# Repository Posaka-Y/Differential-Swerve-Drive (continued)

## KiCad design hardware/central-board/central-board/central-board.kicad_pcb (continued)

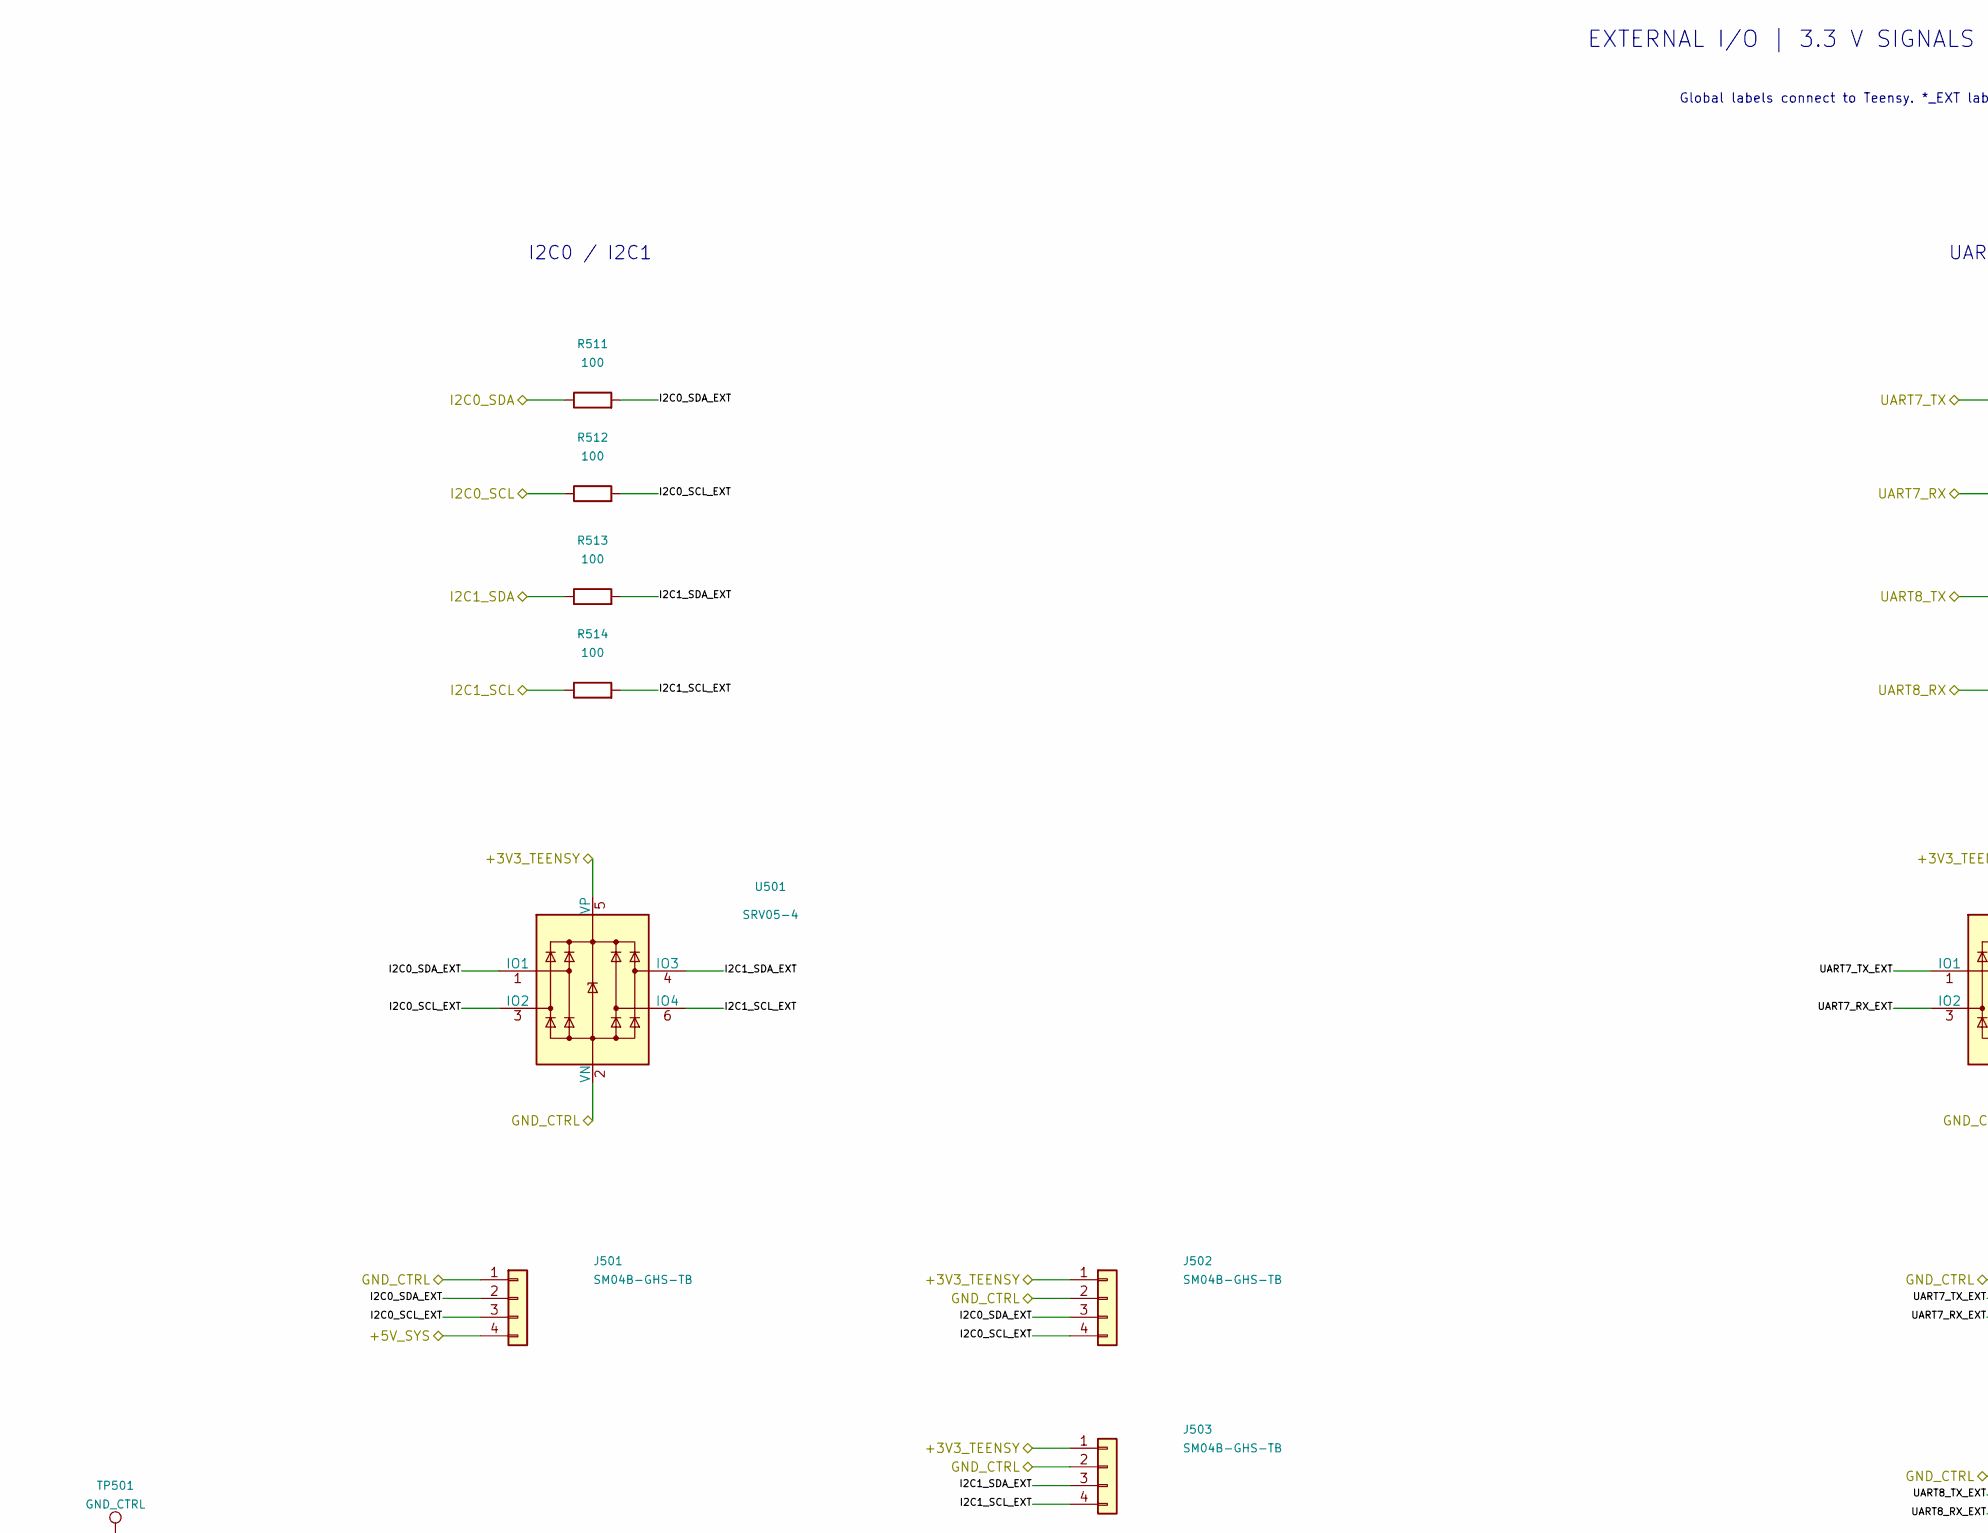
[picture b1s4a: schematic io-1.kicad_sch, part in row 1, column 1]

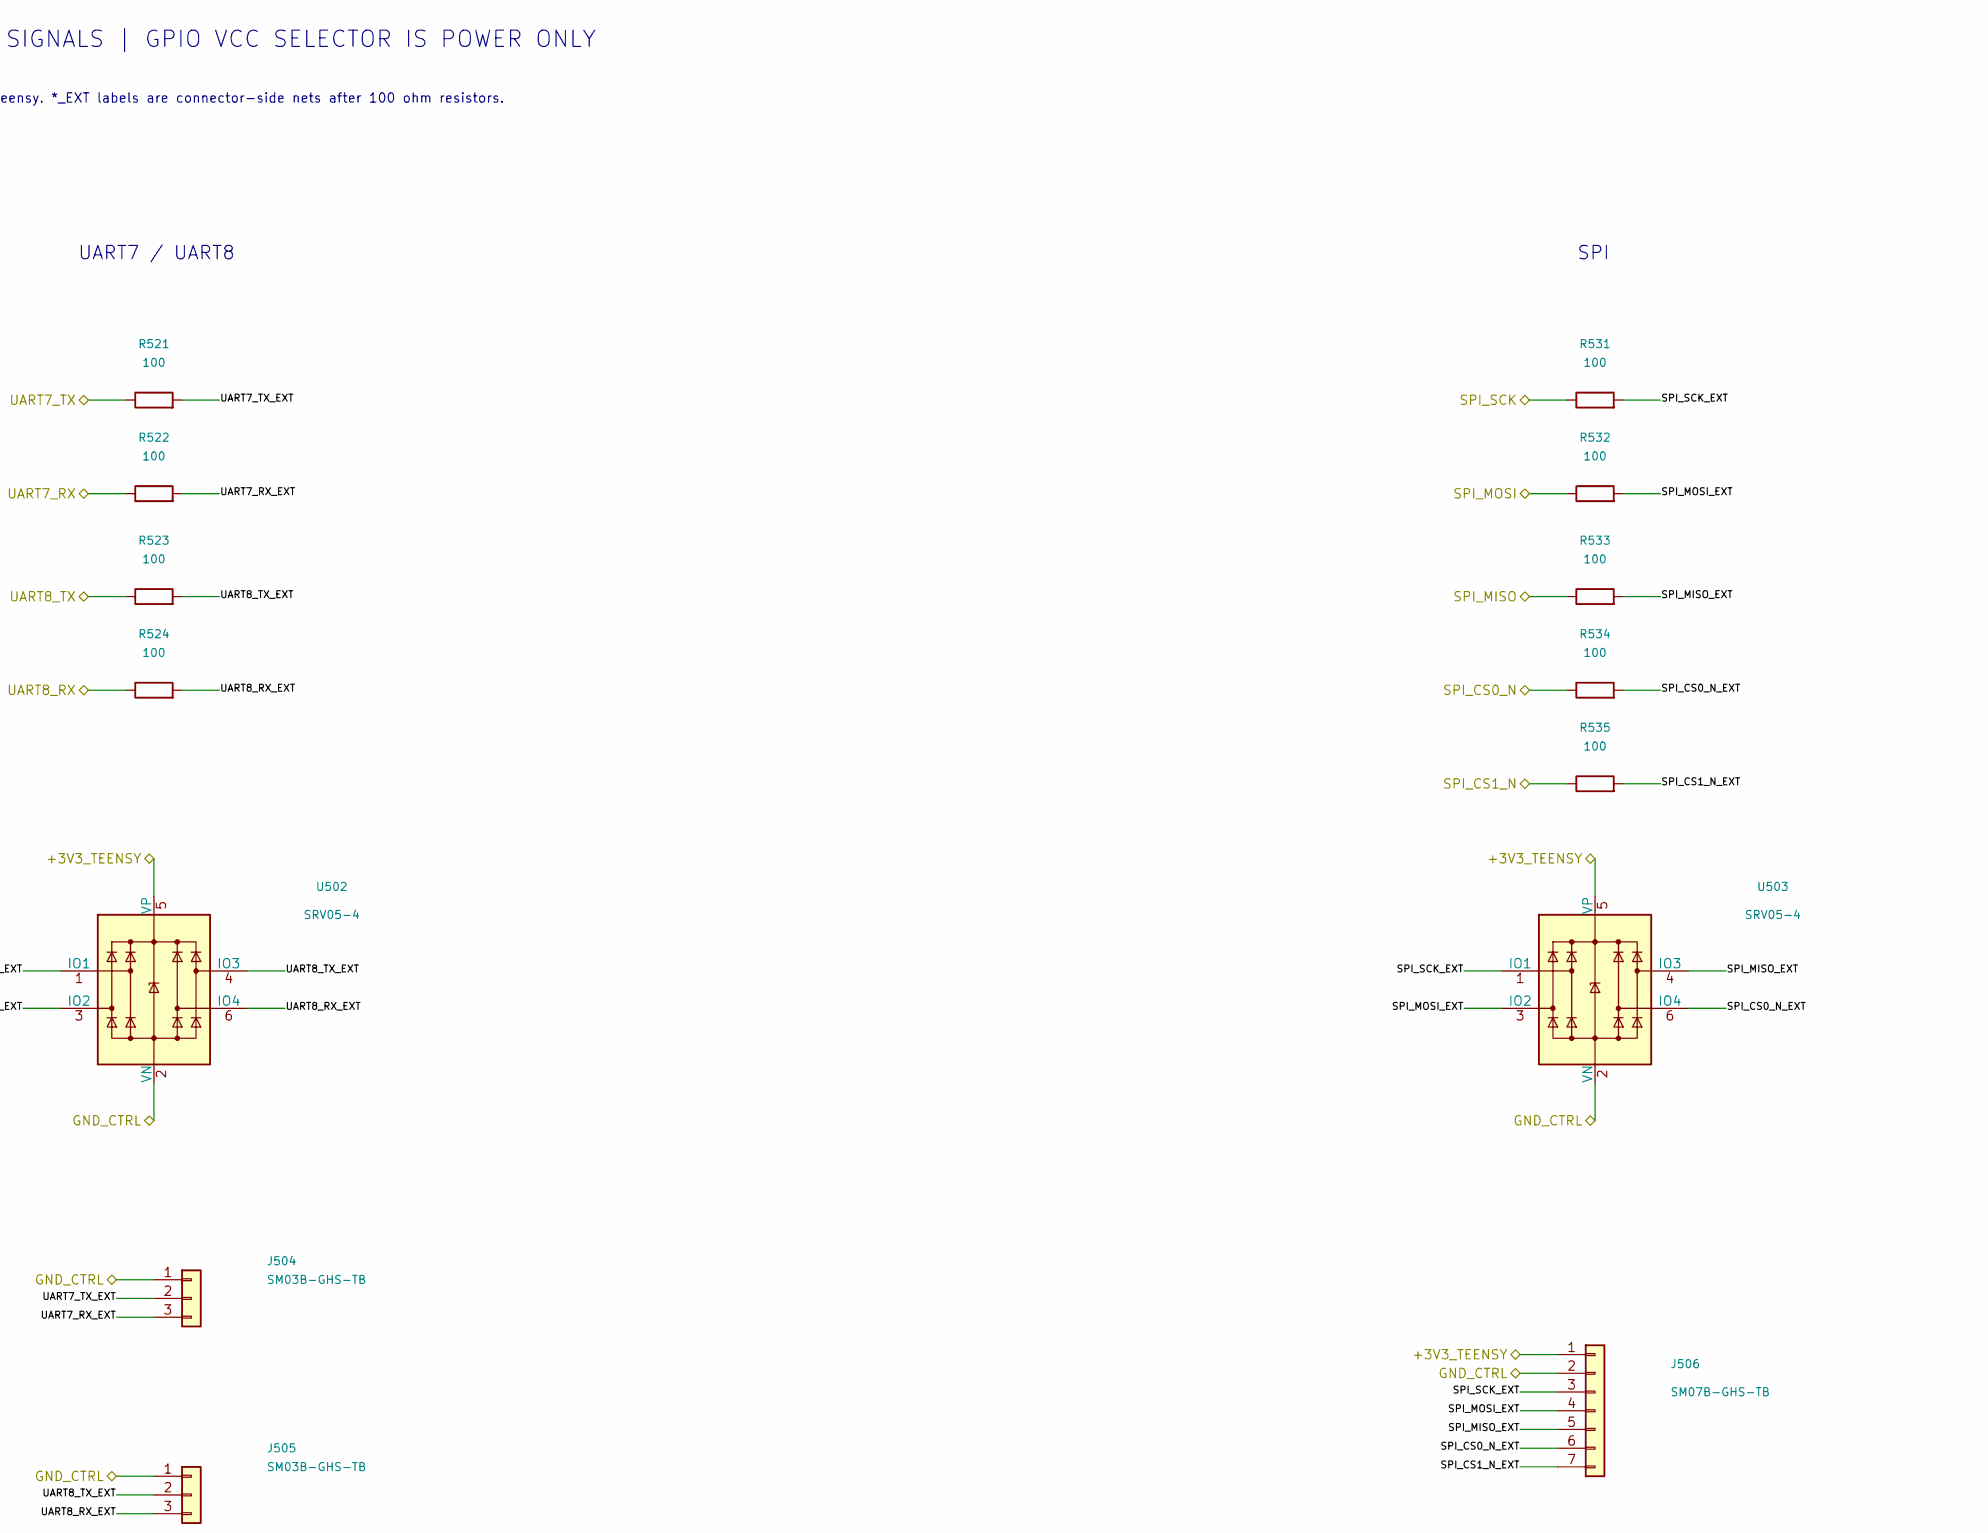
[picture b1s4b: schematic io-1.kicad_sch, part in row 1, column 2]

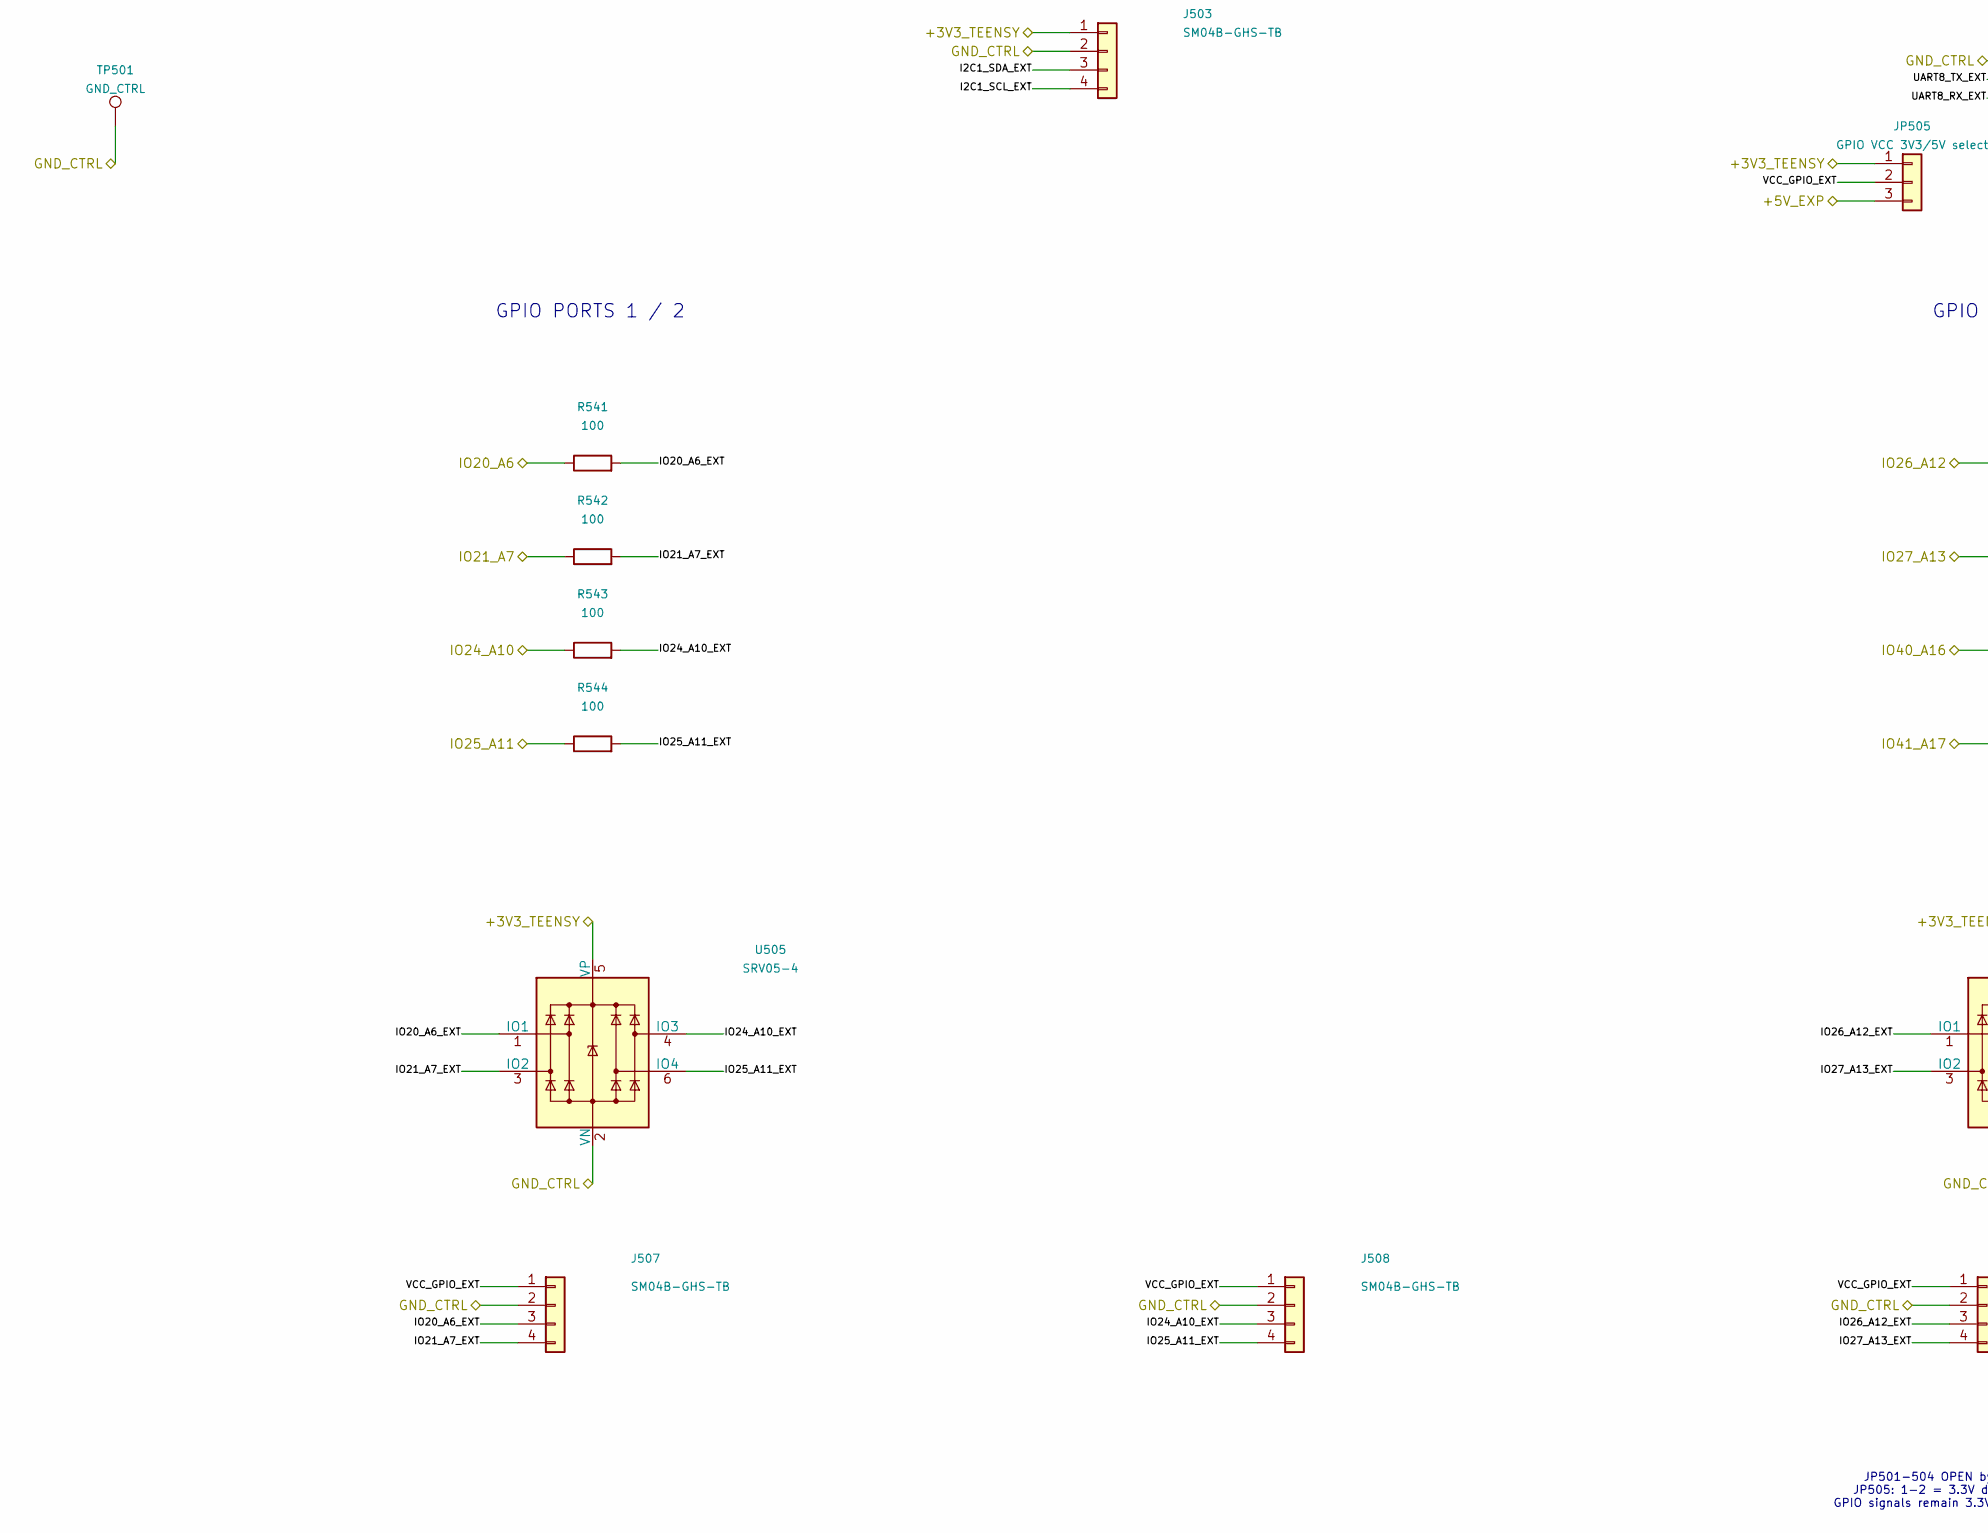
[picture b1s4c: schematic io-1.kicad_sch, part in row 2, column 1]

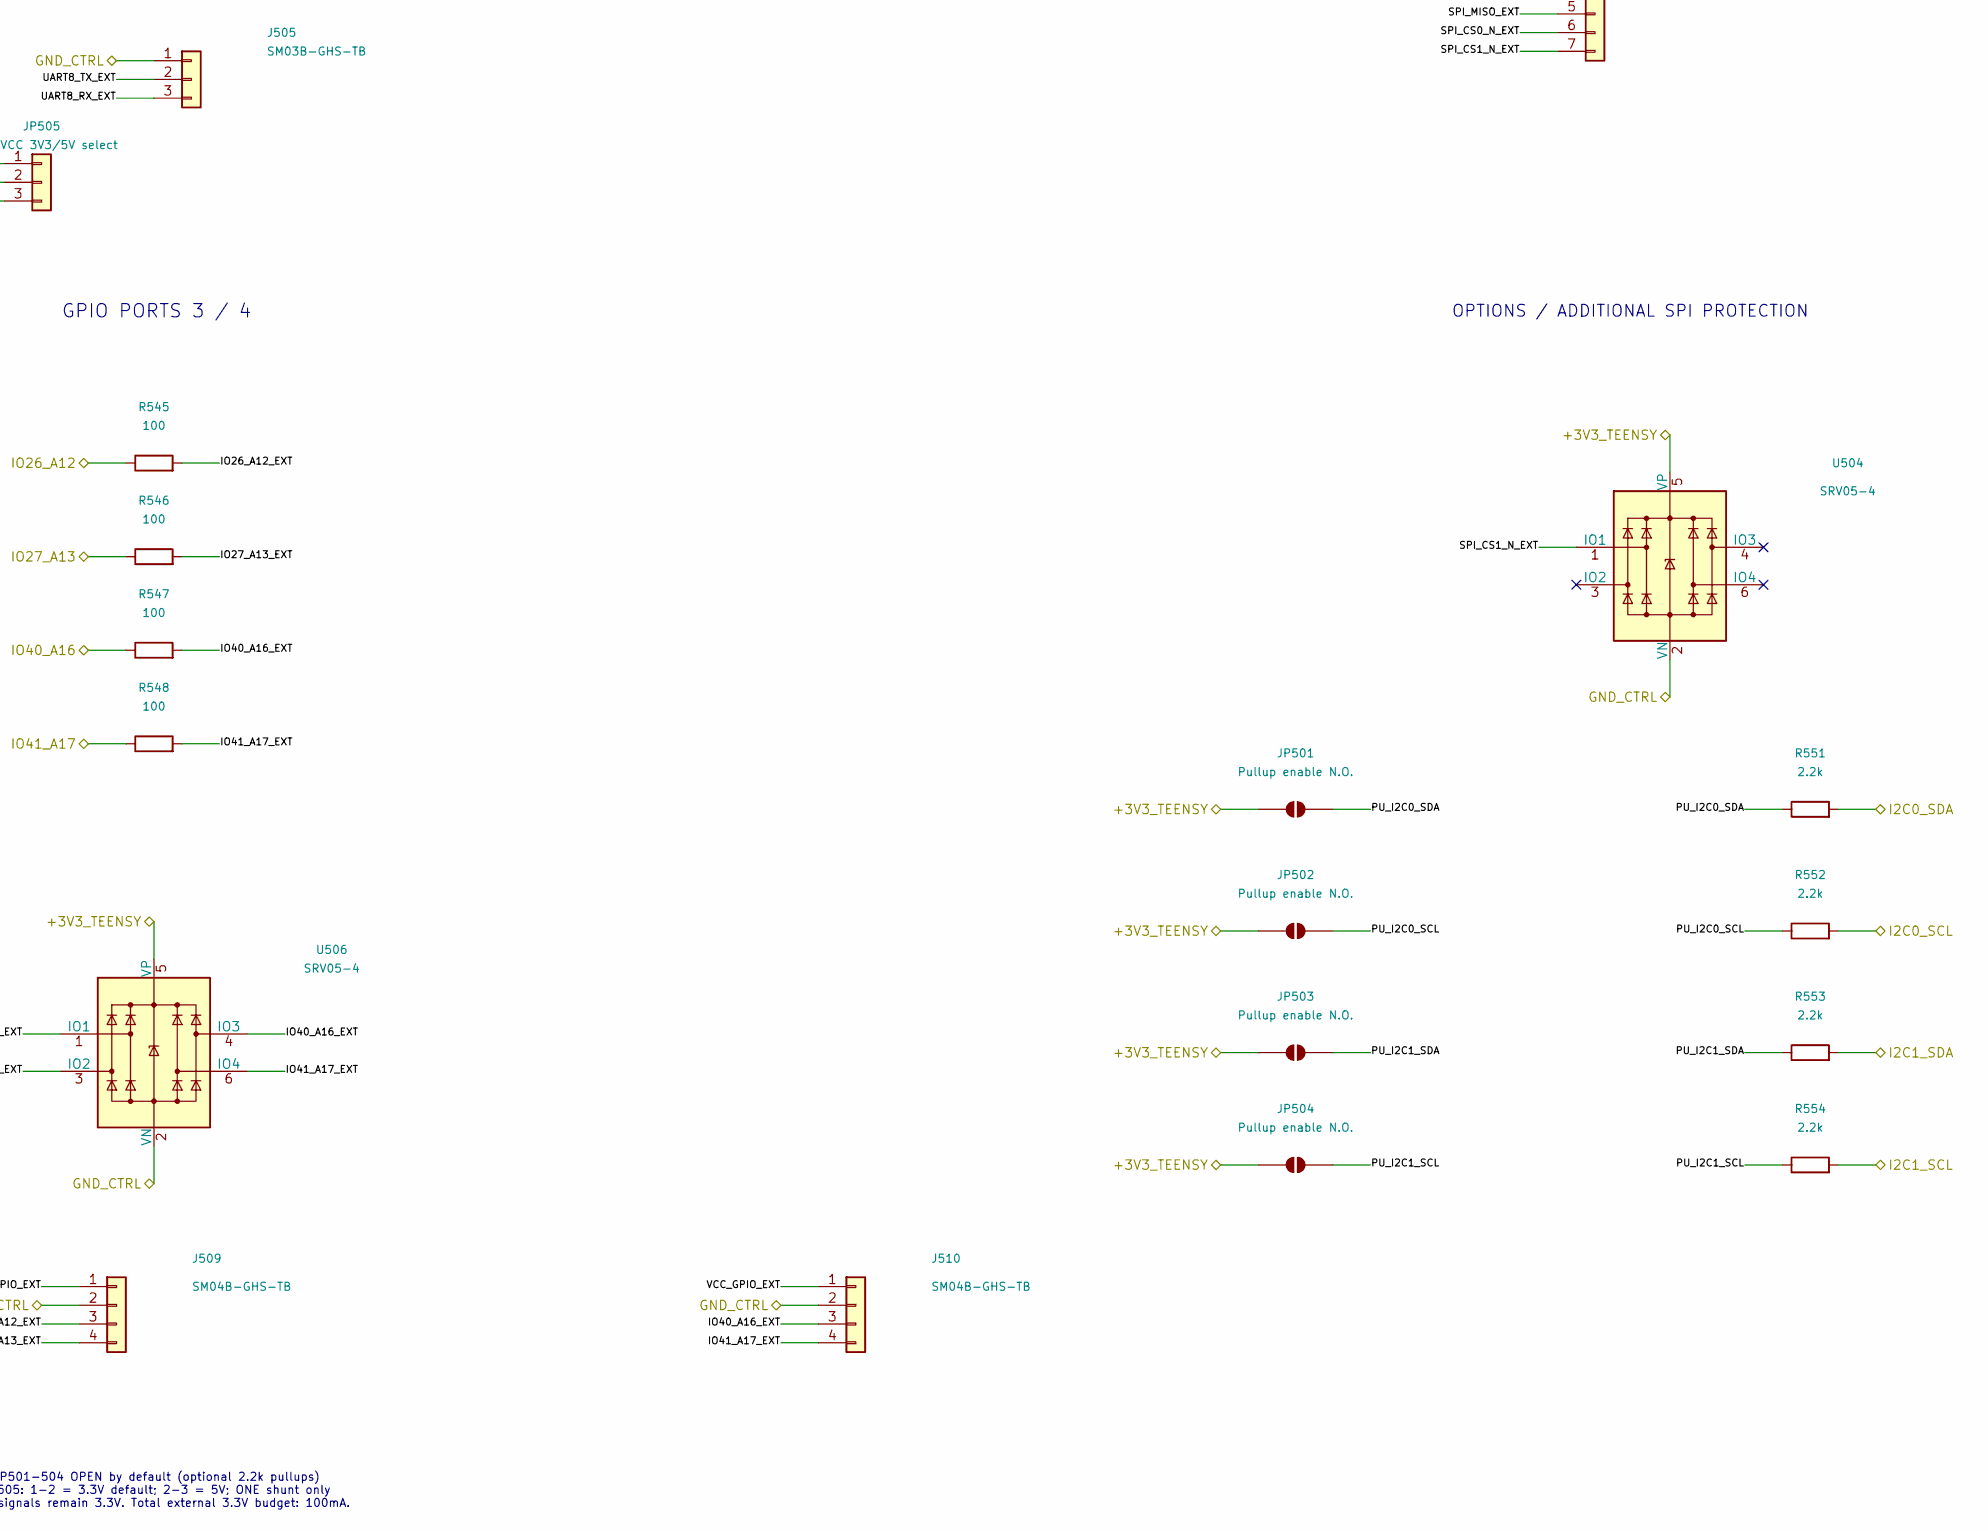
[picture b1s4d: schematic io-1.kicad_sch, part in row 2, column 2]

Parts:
J501, J502, J503, J507, J508, J509, J510: SM04B-GHS-TB; JST_GH_SM04B-GHS-TB_1x04-1MP_P1.25mm_Horizontal
J504, J505: SM03B-GHS-TB; JST_GH_SM03B-GHS-TB_1x03-1MP_P1.25mm_Horizontal
J506: SM07B-GHS-TB; JST_GH_SM07B-GHS-TB_1x07-1MP_P1.25mm_Horizontal
JP501, JP502, JP503, JP504: Pullup enable N.O.; SolderJumper-2_P1.3mm_Open_RoundedPad1.0x1.5mm
JP505: GPIO VCC 3V3/5V select; PinHeader_1x03_P2.54mm_Vertical
R511, R512, R513, R514, R521, R522, R523, R524, R531, R532, R533, R534, R535, R541, R542, R543, R544, R545, R546, R547, R548: 100; R_0603_1608Metric
R551, R552, R553, R554: 2.2k; R_0603_1608Metric
TP501: GND_CTRL; Harwin_S1751-46R
U501, U502, U503, U504, U505, U506: SRV05-4; SOT-23-6

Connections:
/+3V3_TEENSY: J502.1, J503.1, J506.1, JP501.1 (A), JP502.1 (A), JP503.1 (A), JP504.1 (A), JP505.1, U501.5 (VP), U502.5 (VP), U503.5 (VP), U504.5 (VP), U505.5 (VP), U506.5 (VP); also elsewhere on the board
/+5V_EXP: JP505.3; also elsewhere on the board
/+5V_SYS: J501.4; also elsewhere on the board
/I2C0_SCL: R512.1, R552.2; also elsewhere on the board
/I2C0_SDA: R511.1, R551.2; also elsewhere on the board
/I2C1_SCL: R514.1, R554.2; also elsewhere on the board
/I2C1_SDA: R513.1, R553.2; also elsewhere on the board
/IO20_A6: R541.1; also elsewhere on the board
/IO21_A7: R542.1; also elsewhere on the board
/IO24_A10: R543.1; also elsewhere on the board
/IO25_A11: R544.1; also elsewhere on the board
/IO26_A12: R545.1; also elsewhere on the board
/IO27_A13: R546.1; also elsewhere on the board
/IO40_A16: R547.1; also elsewhere on the board
/IO41_A17: R548.1; also elsewhere on the board
/Matek battery monitor / expansion I/O (1)/I2C0_SCL_EXT: J501.3, J502.4, R512.2, U501.3 (IO2)
/Matek battery monitor / expansion I/O (1)/I2C0_SDA_EXT: J501.2, J502.3, R511.2, U501.1 (IO1)
/Matek battery monitor / expansion I/O (1)/I2C1_SCL_EXT: J503.4, R514.2, U501.6 (IO4)
/Matek battery monitor / expansion I/O (1)/I2C1_SDA_EXT: J503.3, R513.2, U501.4 (IO3)
/Matek battery monitor / expansion I/O (1)/IO20_A6_EXT: J507.3, R541.2, U505.1 (IO1)
/Matek battery monitor / expansion I/O (1)/IO21_A7_EXT: J507.4, R542.2, U505.3 (IO2)
/Matek battery monitor / expansion I/O (1)/IO24_A10_EXT: J508.3, R543.2, U505.4 (IO3)
/Matek battery monitor / expansion I/O (1)/IO25_A11_EXT: J508.4, R544.2, U505.6 (IO4)
/Matek battery monitor / expansion I/O (1)/IO26_A12_EXT: J509.3, R545.2, U506.1 (IO1)
/Matek battery monitor / expansion I/O (1)/IO27_A13_EXT: J509.4, R546.2, U506.3 (IO2)
/Matek battery monitor / expansion I/O (1)/IO40_A16_EXT: J510.3, R547.2, U506.4 (IO3)
/Matek battery monitor / expansion I/O (1)/IO41_A17_EXT: J510.4, R548.2, U506.6 (IO4)
/Matek battery monitor / expansion I/O (1)/PU_I2C0_SCL: JP502.2 (B), R552.1
/Matek battery monitor / expansion I/O (1)/PU_I2C0_SDA: JP501.2 (B), R551.1
/Matek battery monitor / expansion I/O (1)/PU_I2C1_SCL: JP504.2 (B), R554.1
/Matek battery monitor / expansion I/O (1)/PU_I2C1_SDA: JP503.2 (B), R553.1
/Matek battery monitor / expansion I/O (1)/SPI_CS0_N_EXT: J506.6, R534.2, U503.6 (IO4)
/Matek battery monitor / expansion I/O (1)/SPI_CS1_N_EXT: J506.7, R535.2, U504.1 (IO1)
/Matek battery monitor / expansion I/O (1)/SPI_MISO_EXT: J506.5, R533.2, U503.4 (IO3)
/Matek battery monitor / expansion I/O (1)/SPI_MOSI_EXT: J506.4, R532.2, U503.3 (IO2)
/Matek battery monitor / expansion I/O (1)/SPI_SCK_EXT: J506.3, R531.2, U503.1 (IO1)
/Matek battery monitor / expansion I/O (1)/UART7_RX_EXT: J504.3, R522.2, U502.3 (IO2)
/Matek battery monitor / expansion I/O (1)/UART7_TX_EXT: J504.2, R521.2, U502.1 (IO1)
/Matek battery monitor / expansion I/O (1)/UART8_RX_EXT: J505.3, R524.2, U502.6 (IO4)
/Matek battery monitor / expansion I/O (1)/UART8_TX_EXT: J505.2, R523.2, U502.4 (IO3)
/Matek battery monitor / expansion I/O (1)/VCC_GPIO_EXT: J507.1, J508.1, J509.1, J510.1, JP505.2
/SPI_CS0_N: R534.1; also elsewhere on the board
/SPI_CS1_N: R535.1; also elsewhere on the board
/SPI_MISO: R533.1; also elsewhere on the board
/SPI_MOSI: R532.1; also elsewhere on the board
/SPI_SCK: R531.1; also elsewhere on the board
/UART7_RX: R522.1; also elsewhere on the board
/UART7_TX: R521.1; also elsewhere on the board
/UART8_RX: R524.1; also elsewhere on the board
/UART8_TX: R523.1; also elsewhere on the board
GND_CTRL: J501.1, J502.2, J503.2, J504.1, J505.1, J506.2, J507.2, J508.2, J509.2, J510.2, TP501.1 (1_1), U501.2 (VN), U502.2 (VN), U503.2 (VN), U504.2 (VN), U505.2 (VN), U506.2 (VN); also elsewhere on the board

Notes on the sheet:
OPTIONS / ADDITIONAL SPI PROTECTION
UART7 / UART8
I2C0 / I2C1
JP501-504 OPEN by default (optional 2.2k pullups) JP505: 1-2 = 3.3V default; 2-3 = 5V; ONE shunt only GPIO signals remain 3.3V. Total external 3.3V budget: 100mA.
GPIO PORTS 3 / 4
SPI
GPIO PORTS 1 / 2
Global labels connect to Teensy. *_EXT labels are connector-side nets after 100 ohm resistors.
EXTERNAL I/O | 3.3 V SIGNALS | GPIO VCC SELECTOR IS POWER ONLY

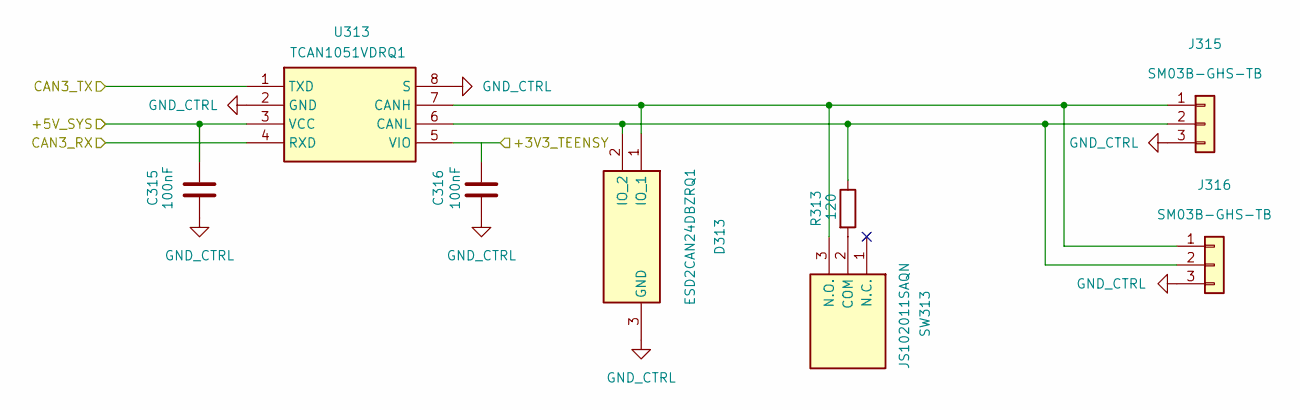
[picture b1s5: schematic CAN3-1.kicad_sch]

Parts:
C315, C316: 100nF; C_0603_1608Metric
D313: ESD2CAN24DBZRQ1; SOT-23
J315, J316: SM03B-GHS-TB; JST_GH_SM03B-GHS-TB_1x03-1MP_P1.25mm_Horizontal
R313: 120; R_0603_1608Metric
SW313: JS102011SAQN
U313: TCAN1051VDRQ1; SOIC-8_3.9x4.9mm_P1.27mm

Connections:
/+3V3_TEENSY: C316.1, U313.5 (VIO); also elsewhere on the board
/+5V_SYS: C315.1, U313.3 (VCC); also elsewhere on the board
/CAN3_RX: U313.4 (RXD); also elsewhere on the board
/CAN3_TX: U313.1 (TXD); also elsewhere on the board
GND_CTRL: C315.2, C316.2, D313.3 (GND), J315.3, J316.3, U313.2 (GND), U313.8 (S); also elsewhere on the board
unnamed: D313.1 (IO_1), J315.1, J316.1, SW313.3 (N.O.), U313.7 (CANH)
unnamed: D313.2 (IO_2), J315.2, J316.2, R313.1, U313.6 (CANL)
unnamed: R313.2, SW313.2 (COM)

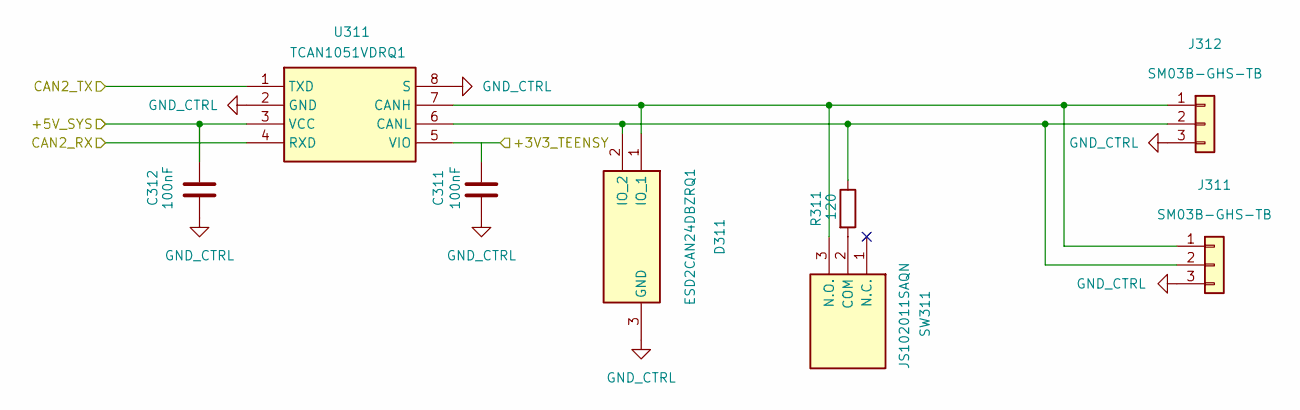
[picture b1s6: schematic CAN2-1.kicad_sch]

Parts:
C311, C312: 100nF; C_0603_1608Metric
D311: ESD2CAN24DBZRQ1; SOT-23
J311, J312: SM03B-GHS-TB; JST_GH_SM03B-GHS-TB_1x03-1MP_P1.25mm_Horizontal
R311: 120; R_0603_1608Metric
SW311: JS102011SAQN
U311: TCAN1051VDRQ1; SOIC-8_3.9x4.9mm_P1.27mm

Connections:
/+3V3_TEENSY: C311.1, U311.5 (VIO); also elsewhere on the board
/+5V_SYS: C312.1, U311.3 (VCC); also elsewhere on the board
/CAN2_RX: U311.4 (RXD); also elsewhere on the board
/CAN2_TX: U311.1 (TXD); also elsewhere on the board
GND_CTRL: C311.2, C312.2, D311.3 (GND), J311.3, J312.3, U311.2 (GND), U311.8 (S); also elsewhere on the board
unnamed: D311.1 (IO_1), J311.1, J312.1, SW311.3 (N.O.), U311.7 (CANH)
unnamed: D311.2 (IO_2), J311.2, J312.2, R311.1, U311.6 (CANL)
unnamed: R311.2, SW311.2 (COM)

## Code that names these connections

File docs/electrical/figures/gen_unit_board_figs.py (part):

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    d.add(elm.Ground())
    note(d, (0.4, -3.0), 'ハーネス側 GND_CTRL = 基板内 GND')

    # pin1 -> PWR_5V_IN
    d.add(elm.Line().at(j101.p1).right().length(2.2).label('PWR_5V_IN', loc='top'))
    din = d.add(elm.Dot())
    d.add(elm.Capacitor().at(din.center).down().length(1.8).label('C101\n2.2uF以上', loc='bottom', fontsize=9))
    d.add(elm.Ground())
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    d.add(elm.Wire('-|').at(u101.CEN).to(dv.center))
    note(d, (7.2, -1.3), 'CE_N=VOUT 接続は意図的\n(RPP+RCB、TI DS 8.3節)\n標準アプリ図(CE_N=GND)と異なる')

    d.add(elm.Line().at(dv.center).right().length(1.2).label('PWR_5V', loc='top'))
    dc1 = d.add(elm.Dot())
    d.add(elm.Capacitor().at(dc1.center).down().length(1.8).label('C201\n100nF', loc='bottom', fontsize=9))
    d.add(elm.Ground())
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        size=(3.0, 5.4)).at((0, 0)).anchor('TXD').label('U401\nTCAN1051VDRQ1\n(SOIC-8)', loc='top', fontsize=9))

    # MCU side
    d.add(elm.Line(arrow='->').at((-3.5, 0)).to(u401.TXD).label('COMM_TX', loc='top', fontsize=9))
    netlabel(d, (-3.5, 0), 'U301 PA12\n(FDCAN1_TX)', loc='left')
    ry = u401.RXD.y
    d.add(elm.Line(arrow='->').at(u401.RXD).to((-3.5, ry)).label('COMM_RX', loc='top', fontsize=9))
    netlabel(d, (-3.5, ry), 'U301 PA11\n(FDCAN1_RX)', loc='left')

    # VCC (5V) + C401
    vy = u401.VCC.y
    d.add(elm.Line().at(u401.VCC).to((-2.6, vy)))
    dvcc = d.add(elm.Dot().at((-1.6, vy)))
    netlabel(d, (-2.6, vy), 'PWR_5V', loc='left')
    d.add(elm.Capacitor().at(dvcc.center).down().length(1.4).label('C401\n100nF', loc='bottom', fontsize=8))
    d.add(elm.Ground())
    # VIO (3V3) + C402
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    ly = u401.CANL.y     # y of COMM_B
    hx0 = u401.CANH.x
    lx0 = u401.CANL.x
    d.add(elm.Line().at(u401.CANH).right().length(2.0).label('COMM_A', loc='top', fontsize=10))
    d.add(elm.Line().right().length(10.0))
    hx_end = hx0 + 12.0
    d.add(elm.Line().at(u401.CANL).right().length(2.0).label('COMM_B', loc='top', fontsize=10))
    d.add(elm.Line().right().length(9.0))
    lx_end = lx0 + 11.0

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    note(d, (hx_end + 0.2, hy - 8.4), 'J401/J402はIN/OUT区別なく並列直結(パススルー)。\nGND(3番)は省略しない')

    note(d, (-4.9, ly - 7.6),
         'C620側 (U501/D501/R501/SW501): 同一回路。C620_CAN_TX=PB13(FDCAN2_TX)、C620_CAN_RX=PB12(FDCAN2_RX)、\n'
         '外部ネット名 C620_CAN_H/L。コネクタ型番・個数・ピン順は未確定(正本6章#1)のため描いていない。')
    save(d, 'unit-board-block2')

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
    # --- NRST ---
    y2 = -5.2
    netlabel(d, (0, y2), 'U301 PG10-NRST (pin 7)', loc='left')
    d.add(elm.Line().at((0, y2)).right().length(1.6))
    dn = d.add(elm.Dot())
    d.add(elm.Capacitor().at(dn.center).down().length(1.6).label('C313\n100nF', loc='bottom', fontsize=8))
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
    # --- BOOT0 ---
    x3 = 9.0
    netlabel(d, (x3, y2), 'U301 PB8-BOOT0', loc='left')
    d.add(elm.Line().at((x3, y2)).right().length(1.6))
    db = d.add(elm.Dot())
    d.add(elm.Resistor().at(db.center).down().length(2.0).label('R303\n10kΩ', loc='bottom', fontsize=8))
    d.add(elm.Ground())
    d.add(elm.Line().at(db.center).right().length(1.8))
    netlabel(d, d.here, 'TP(BOOT0)+隣接TP(3V3)', loc='right')
    note(d, (x3 + 0.2, y2 - 3.0), 'pull-down。PB8はGPIOに使わない')

    save(d, 'unit-board-block4')

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    d = schemdraw.Drawing(show=False)
    d.config(fontsize=10, font=FONT)
    d.add(elm.Label().at((0, 3.6)).label(
        'Block 5: 5V監視ADC (PA0)', loc='right', halign='left', fontsize=12))

    netlabel(d, (0, 0), 'PWR_5V', loc='left')
    d.add(elm.Resistor().at((0, 0)).right().length(2.4).label('R304 33kΩ', loc='top', fontsize=9))
    dm = d.add(elm.Dot())
    d.add(elm.Resistor().at(dm.center).down().length(2.2).label('R305\n22kΩ', loc='bottom', fontsize=9))
    d.add(elm.Ground())
    d.add(elm.Line().at(dm.center).right().length(1.6).label('ADC_5V_MON', loc='top', fontsize=10))
    dc = d.add(elm.Dot())
    d.add(elm.Capacitor().at(dc.center).down().length(2.2).label('C314\n10nF', loc='bottom', fontsize=9))
    d.add(elm.Ground())
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    d.add(elm.Line().at(dc.center).right().length(1.8))
    dd = d.add(elm.Dot())
    d.add(elm.Line().at(dd.center).right().length(1.8))
    netlabel(d, d.here, 'U301 PA0 (ADC)\nmax 2.2V (0.4倍)', loc='right')

    # BAT54S: pin1=GND, pin2=3V3, pin3=PA0
    x = dd.center.x
    d1 = d.add(elm.Schottky().at((x, 0)).up().length(1.8).label('', loc='top'))
    d.add(elm.Line().up().length(0.4))
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    d.add(elm.Label().at((x + 0.25, 0.1)).label('3', loc='right', fontsize=8))
    d.add(elm.Label().at((x + 0.25, -1.9)).label('1', loc='right', fontsize=8))
    note(d, (x + 1.6, -1.0),
         'D301 BAT54SLT1G (直列2素子)\npin1=GND / pin2=3V3 / pin3=PA0\n上下クランプ。内部ダイオード向きを\nデータシート図と必ず照合')
    note(d, (0, -4.4), '5V系がADCへ入る唯一の点。サンプリング時間は\nソースインピーダンス13.2kΩに合わせる(ファーム)')
    save(d, 'unit-board-block5')

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        .label('J601\nSM06B-GHS-TB\n(AMT22中継/横挿し)', loc='top', fontsize=9))

    d.add(elm.Line().at(j601.p1).right().length(4.6))
    netlabel(d, d.here, 'PWR_5V', loc='right')
    d.add(elm.Resistor().at(j601.p2).right().length(2.6).label('R601', loc='top', fontsize=8))
    d.add(elm.Line().right().length(2.0))
    netlabel(d, d.here, 'SPI3_SCK (U301 PC10)', loc='right')
    d.add(elm.Resistor().at(j601.p3).right().length(2.6).label('R602', loc='top', fontsize=8))
    d.add(elm.Line().right().length(2.0))
    netlabel(d, d.here, 'SPI3_MOSI (U301 PC12)', loc='right')
    d.add(elm.Line().at(j601.p4).right().length(0.4))
    d.add(elm.Ground())
    d.add(elm.Resistor().at(j601.p5).right().length(2.6).label('R603', loc='top', fontsize=8))
    d.add(elm.Line().right().length(2.0))
    netlabel(d, d.here, 'SPI3_MISO (U301 PC11)', loc='right')
    d.add(elm.Resistor().at(j601.p6).right().length(2.6).label('R604', loc='top', fontsize=8))
    d.add(elm.Line().right().length(2.0))
    netlabel(d, d.here, 'AMT22_CS_N (U301 PD2, ソフトCS)', loc='right')
    note(d, (0, -6.6),
         'AMT22と同ピン順=ストレート結線。R601-604は0603フットプリントのみ確定、\n'
         '値は未確定(初期0Ω実装が候補、正本6章#3)。5V電源・3.3V論理で直結成立')
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        elm.IcPin(name='SWCLK', pin='2', side='right', slot='5/6', anchorname='p2'),
        elm.IcPin(name='SWDIO', pin='3', side='right', slot='4/6', anchorname='p3'),
        elm.IcPin(name='NRST', pin='4', side='right', slot='3/6', anchorname='p4'),
        elm.IcPin(name='DBG_TX', pin='5', side='right', slot='2/6', anchorname='p5'),
        elm.IcPin(name='DBG_RX', pin='6', side='right', slot='1/6', anchorname='p6')],
        size=(2.4, 5.6)).at((xj, 0)).anchor('p1')
        .label('J701\nBM06B-GHS-TBT\n(デバッグ/上挿し)', loc='top', fontsize=9))
    d.add(elm.Line().at(j701.p1).right().length(0.8))
    d.add(elm.Ground())
    for pin, name in [('p2', 'SWCLK (U301 PA14)'), ('p3', 'SWDIO (U301 PA13)'),
                      ('p4', 'NRST (U301 PG10 pin7)'),
                      ('p5', 'DBG_TX (U301 PA2, LPUART1_TX)'),
                      ('p6', 'DBG_RX (U301 PA3, LPUART1_RX)')]:
        d.add(elm.Line().at(getattr(j701, pin)).right().length(1.6))
        netlabel(d, d.here, name, loc='right')
    note(d, (xj, -6.6),
         'DBG_TX/RX方向は「基板視点TX/RX」の推測=未確定(正本6章#7)。\n'
         'WeActデバッガ側と照合のこと。J701に電源ピン無し=デバッガ給電を\n'
         '基板へ入れない(意図的)。PA13/PA14はSWD専用')

    # ---- SW701 ID DIP ----
    ys = -10.0
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        .label('SW701 3bit DIP\n(型番未確定 6章#2)', loc='top', fontsize=9))
    d.add(elm.Line().at(sw.com).left().length(0.8))
    d.add(elm.Ground())
    for pin, name in [('b0', 'UNIT_ID0 (U301 PC6)'), ('b1', 'UNIT_ID1 (U301 PC7)'),
                      ('b2', 'UNIT_ID2 (U301 PC8)')]:
        d.add(elm.Line().at(getattr(sw, pin)).right().length(1.6))
        netlabel(d, d.here, name, loc='right')
    note(d, (0, ys - 3.2), '内部プルアップ、ON=GND短絡\n→ ON=Low、ファームで読み値反転')
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    # ---- LEDs ----
    xl = 10.5
    rows = [('3V3 (常時点灯)', 'R701\n1kΩ', 'D701 PWR 緑'),
            ('LED_RUN (U301 PA5)', 'R702\n1kΩ', 'D702 RUN 緑'),
            ('LED_COMM (U301 PB10)', 'R703\n1kΩ', 'D703 COMM 黄'),
            ('LED_ERR (U301 PB11)', 'R704\n1kΩ', 'D704 ERR 赤')]
    for i, (src, rr, dd) in enumerate(rows):
        y = ys + 1.2 - i * 1.9
        netlabel(d, (xl, y), src, loc='left')
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
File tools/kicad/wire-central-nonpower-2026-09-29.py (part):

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s.text('24 V LOOP & EXTERNAL CONNECTORS',135,35,1.8)
for r,x,y,l,v,nets in [
 ('J403',105,60,None,None,['+24V_CTRL_IN','GND_24V_RETURN']),
 ('J401',255,65,'Connector_Generic:Conn_01x04','TBD E-stop 4pin',['ESTOP_LOOP_OUT','ESTOP_LOOP_RETURN','ESTOP_LED_24V','GND_CTRL_LED']),
 ('J402',410,60,None,None,['ESTOP_LOOP_RETURN','COIL_NEG'])]:
    s.place(r,x,y,libid=l,value=v,footprint='' if r=='J401' else None,template='J403')
    for i,n in enumerate(nets,1):s.connect(r,i,n)
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s.text('5 V BUFFER -> 100 V MOSFET / DEFAULT OFF',420,172,1.8)
s.place('U402',350,210);s.connect('U402',1,'GND_CTRL');s.connect('U402',2,'MOTOR_PWR_EN',True)
s.connect('U402',3,'GND_CTRL');s.connect('U402',5,'+5V_SYS',True)
s.place('R414',405,210,90);a,_=s.point('U402',4);b,_=s.point('R414',1);s.wire(a,b);s.label('COIL_BUFFER_OUT',(380,210),False)
expected['U402.4']=expected['R414.1']='COIL_BUFFER_OUT'
s.place('Q401',475,210);a,_=s.point('R414',2);b,_=s.point('Q401',1);s.wire(a,b);s.label('COIL_GATE',(430,210),False)
expected['R414.2']=expected['Q401.1']='COIL_GATE'
s.connect('Q401',3,'COIL_NEG');s.connect('Q401',2,'GND_24V_RETURN')
for r,x,n in [('R413',315,'MOTOR_PWR_EN'),('R415',425,'COIL_GATE')]:
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s.place('C401',520,265);s.connect('C401',1,'+5V_SYS',True);s.connect('C401',2,'GND_CTRL')

# Explicit unfitted design blocks: no invented selected part / manufacturing footprint.
custom={'lib_id':'CentralPlacement:CoilClamp_TBD','value':'CLAMP TBD','custom_pins':[{'number':1,'name':'COIL_POS'},{'number':2,'name':'COIL_NEG'}]}
libs.add_custom(custom)
s.place('X401',465,115,libid=custom['lib_id'],value='CLAMP TBD',footprint='',template='J403')
s.connect('X401',1,'ESTOP_LOOP_RETURN');s.connect('X401',2,'COIL_NEG')
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 ('I2C0 / I2C1',100,45,[(511,'I2C0_SDA'),(512,'I2C0_SCL'),(513,'I2C1_SDA'),(514,'I2C1_SCL')],501),
 ('UART7 / UART8',295,45,[(521,'UART7_TX'),(522,'UART7_RX'),(523,'UART8_TX'),(524,'UART8_RX')],502),
 ('SPI',490,45,[(531,'SPI_SCK'),(532,'SPI_MOSI'),(533,'SPI_MISO'),(534,'SPI_CS0_N'),(535,'SPI_CS1_N')],503),
 ('GPIO PORTS 1 / 2',100,245,[(541,'IO20_A6'),(542,'IO21_A7'),(543,'IO24_A10'),(544,'IO25_A11')],505),
 ('GPIO PORTS 3 / 4',295,245,[(545,'IO26_A12'),(546,'IO27_A13'),(547,'IO40_A16'),(548,'IO41_A17')],506)]
for title,x,y,signals,tvs in groups:
    s.text(title,x,y,1.8)
    for i,(num,net) in enumerate(signals):
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
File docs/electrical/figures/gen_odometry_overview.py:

# -*- coding: utf-8 -*-
"""
Odometry board zone/block overview diagram (schemdraw SVG rendering).
Source of truth: docs/electrical/ODOMETRY_BOARD_SCHEMATIC_REFERENCE.md
  Section "1枚上の配置" / "RefDes割当" / "ブロック接続".
Generated: 2026-07-25

Box + arrow + net-name level only (no IC pin layout, no R/C values).
"""
import os
import matplotlib
from matplotlib import font_manager

FONT = 'sans-serif'
for fam in ['Yu Gothic', 'Meiryo', 'MS Gothic']:
    try:
        font_manager.findfont(fam, fallback_to_default=False)
        matplotlib.rcParams['font.family'] = [fam, 'sans-serif']
        FONT = fam
        print('using font', fam)
        break
    except Exception:
        continue

import schemdraw
import schemdraw.elements as elm
from schemdraw.elements import Rect

FIGDIR = os.path.dirname(os.path.abspath(__file__))

BOX_KW = dict(lw=1.3)


def box(d, xy, w, h, title, body='', title_size=11, body_size=9):
    x, y = xy
    d.add(Rect(corner1=(x, y), corner2=(x + w, y + h), **BOX_KW))
    d.add(elm.Label().at((x + w / 2, y + h - 0.35)).label(
        title, halign='center', valign='top', fontsize=title_size))
    if body:
        d.add(elm.Label().at((x + w / 2, y + h - 0.9)).label(
            body, halign='center', valign='top', fontsize=body_size, color='#333333'))
    return (x, y, w, h)


def arrow(d, p1, p2, label='', loc='top', fontsize=9, color='black'):
    d.add(elm.Arrow().at(p1).to(p2).color(color).label(label, loc=loc, fontsize=fontsize))


def main():
    d = schemdraw.Drawing(show=False)
    d.config(fontsize=10, font=FONT)

    d.add(elm.Label().at((0, 15.6)).label(
        'オドメトリ基板(STM32F405RGT6) ゾーン/ブロック概観図 — '
        'ODOMETRY_BOARD_SCHEMATIC_REFERENCE.md 準拠(簡易版・ピン配置/定数は省略)',
        loc='right', halign='left', fontsize=12))

    # ---------------- Top row: power chain -> CAN (100/200/300/400台) ----------------
    top_y = 12.6
    b_pwr = box(d, (0, top_y), 3.4, 2.2, 'J101 5V入力\n逆接/逆流保護', '100番台\nLM66100')
    b_ldo = box(d, (4.6, top_y), 3.4, 2.2, '3.3V LDO', '200番台\nTLV1117LV33')
    b_can = box(d, (16.4, top_y), 3.6, 2.2, 'センサーCAN', '400番台\nTCAN1051V')

    # ---------------- Mid row: Debug | MCU | IMU (700/300/600台) ----------------
    mid_y = 8.4
    b_dbg = box(d, (0, mid_y), 3.4, 2.6, 'Debug/BOOT/\nID/LED', '700番台\nSWD, UNIT_ID, LED x3')
    b_mcu = box(d, (7.4, mid_y - 0.3), 5.6, 3.2, 'STM32F405RGT6', '300番台\nF405最小回路(HSE/NRST/\nVDDA/VCAP)')
    b_imu = box(d, (16.4, mid_y), 3.6, 2.6, 'ICM-42688-P', '600番台\nSPI3 IMU')

    # ---------------- Bottom row: AMT102 x3 (500台) ----------------
    bot_y = 4.2
    b_w1 = box(d, (0, bot_y), 3.6, 2.4, 'AMT102\nWheel 1', 'J501/D501/U501\nR511-512')
    b_w2 = box(d, (5.4, bot_y), 3.6, 2.4, 'AMT102\nWheel 2', 'J502/D502/U502\nR513-514')
    b_w3 = box(d, (10.8, bot_y), 3.6, 2.4, 'AMT102\nWheel 3', 'J503/D503/U503\nR515-516')

    # ================= Arrows: power flow (top row, left to right) =================
    # Drawn below the box bottoms (y < top_y) so the label never overlaps box body text.
    arrow(d, (3.4, top_y - 0.6), (4.6, top_y - 0.6), 'PWR_5V_IN→PWR_5V')

    # PWR_5V continues right along the top to CAN transceiver VCC, and down into
    # the encoder buffers; drawn as a bus line rather than one arrow per box.
    d.add(elm.Line().at((8.0, top_y + 1.1)).right().to((16.4, top_y + 1.1)))
    d.add(elm.Label().at((12.0, top_y + 1.3)).label('PWR_5V (CAN VCC, AMT102 VCC)', fontsize=9, halign='center'))

    # 3V3 rail drop from LDO box down to MCU / Debug / IMU / CAN VIO
    d.add(elm.Line().at((6.3, top_y)).down().to((6.3, mid_y + 2.9)))
    d.add(elm.Line().at((6.3, mid_y + 2.9)).right().to((7.4, mid_y + 2.9)))
    d.add(elm.Label().at((6.3, mid_y + 3.3)).label('3V3', fontsize=9, halign='center'))

    # ================= Arrows: mid row signal connections =================
    arrow(d, (3.4, mid_y + 1.3), (7.4, mid_y + 1.3), 'SWCLK/SWDIO/NRST\nDBG_TX/RX, UNIT_ID0-2\nLED_RUN/COMM/ERR', fontsize=8)
    arrow(d, (13.0, mid_y + 1.3), (16.4, mid_y + 1.3), 'SPI3_SCK/MISO/MOSI\nIMU_CS_N, IMU_INT1/2', fontsize=8)
    arrow(d, (13.0, top_y + 0.3), (16.4, top_y + 0.3), 'COMM_TX/COMM_RX', fontsize=8)

    # ================= Arrows: bottom row encoders up into MCU =================
    for bx, label in [((1.8, bot_y + 2.4), 'W1_A/W1_B\n(TIM2)'),
                       ((7.2, bot_y + 2.4), 'W2_A/W2_B\n(TIM3)'),
                       ((12.6, bot_y + 2.4), 'W3_A/W3_B\n(TIM4)')]:
        arrow(d, bx, (bx[0], mid_y - 0.3), label, loc='right', fontsize=8)

    # ================= External connectors / net legend =================
    d.add(elm.Label().at((0, 1.6)).label(
        'COMM_A/COMM_B: J401↔J402 完全並列パススルー(センサーCAN)。'
        '電源: PWR_5V_IN→PWR_5V→3V3。GNDは全ブロック共通。',
        halign='left', fontsize=9, color='#444444'))
    d.add(elm.Label().at((0, 1.1)).label(
        '詳細ピン割当・部品定数は STM32F405_ODOMETRY_PIN_ASSIGNMENT.md /'
        ' ODOMETRY_BOARD_SCHEMATIC_REFERENCE.md を参照。',
        halign='left', fontsize=9, color='#444444'))

    d.save(os.path.join(FIGDIR, 'odometry-board-overview.svg'))
    if os.environ.get('GEN_FIGS_PNG'):
        d.save(os.path.join(FIGDIR, 'odometry-board-overview.png'), dpi=130)
    print('saved odometry-board-overview.svg')


if __name__ == '__main__':
    main()
